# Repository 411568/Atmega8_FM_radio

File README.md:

<h2>🧐 Features</h2>

This project is a revision of one of my old designs, created a long long time ago when atmel atmega chips where still dirty cheap.

It contains two seperate boards: 
 - main_radio_board - this one contains an Atmega8 microcontroller, TEA5767 FM radio module, PAM8302 amplifier module and power connector. 
 - display_and_controls_board - this one is specificly designed to fit in an old Unitra radio case, it has LEDs used as radio frequency indicators, rotary encoder for changing the frequency, potentiometer for volume and some additional buttons.

<h2>📱 Electronics design</h2>

My FM radio is based on the TEA7567 module, that is connected to an Atmega8A-PU microconotroller via I2C. Then it's output goes to the connector, then on the main panel passes through a logarithmic potentiometer for volume control 
and comes back to the PAM8302 D-class amplifier module. I chose it because it works well with my speaker, which is the one used in the original Unitra radio (it is probably over 40 years old and still works very well).

The schematic and PCB were both designed using KiCAD 6.0

<h2>💈 Connector pinouts</h2>

In the image above you can see the 9V DC input jack location, the speaker output connector and two pin headers (IDC connectors).

J4 connector pinout (all of these are generic GPIO pins of the Atmega8):
* 1  - switch 3
* 2  - switch 1
* 3  - NC
* 4  - LE(ED1)
* 5  - SDI
* 6  - switch 4
* 7  - switch 2
* 8  - switch 0
* 9  - OE(ED2)
* 10 - CLK

J3 connector pinout:
* 1  - TEA5767 output (to potentiometer)
* 2  - transistor 0
* 3  - transistor 2
* 4  - encoder B
* 5  - 5V DC
* 6  - 9V DC
* 7  - PAM8302 input (from potentiometer)
* 8  - GND
* 9  - transistor 1
* 10 - encoder A

<h2>📧 Atmega code</h2>

The code is split into several files, you can find them all on my github. 
* encoder.c - containing functions for interfacing with the rotary encoder
* i2c_lib.c - bit banging i2c library
* led_screen.c - functions for interfacing with led driver
* tea5767.c - functions for the TEA5767 FM radio module
* main.c - main program

Main function for the tea5767 is the send_freq function that tells the module to set a certain frequency:

```c
void send_freq()
{
	unsigned char frequencyH;
	unsigned char frequencyL;
	unsigned int frequencyB;

	frequencyB = 4 * (frequency * 1000000 + 225000) / 32768;
	frequencyH = frequencyB >> 8;
	frequencyL = frequencyB & 0xFF;

    //data transmition 
    I2C_Start();
	I2C_Write(TEA5767_ADDRESS_W);
	I2C_Write(frequencyH);
	I2C_Write(frequencyL);
	I2C_Write(0xB0);
	I2C_Write(0x10);
	I2C_Write(0x00);
    I2C_Stop();

    _delay_ms(10);
}
```

and the search function:

```c
void search(uint8_t direction)
{
	unsigned char frequencyH;
	unsigned char frequencyL;
	unsigned int frequencyB;
    double temp = 88.0;

    if(direction == 1)
    {
        temp = frequency + 0.1; 
    }
    else
    {
        temp = frequency - 0.1; 
    }

	frequencyB = 4 * (temp * 1000000 + 225000) / 32768;
	frequencyH = frequencyB >> 8;
	frequencyL = frequencyB & 0xFF;

    I2C_Start();
	I2C_Write(TEA5767_ADDRESS_W); //send address for writing
	I2C_Write(frequencyH |= 0b01000000); //search mode
	I2C_Write(frequencyL);
    if(direction == 1)
    {
        I2C_Write(0b11010000); //search up with mid adc 
    }
    else
    {
        I2C_Write(0b01010000); //search down with mid adc
    }
	I2C_Write(0x10);
	I2C_Write(0x00);

    I2C_Stop();

    _delay_ms(10);
}
```

You can find what the specific bytes being sent to the module mean in its datasheet.

In the main program loop we check the encoder status:

```c
if(val != val_tmp)
{
    if( (val == 3 && val_tmp == 1) || (val == 0 && val_tmp == 2) )
    {
        if(frequency < 108.0)
        {
            frequency += 1.0;
            send_freq(); 
            display(frequency); //display the current frequency
            search(1); //search up from the set freq
        }
    }
    else if( (val == 2 && val_tmp == 0) || (val == 1 && val_tmp == 3) )
    {
        if(frequency > 88.0)
        {
            frequency -= 1.0;
            send_freq();
            display(frequency); //display the current frequency
            search(0); //search down from the set freq
        }
    }
}
```
and change the frequency by 1Hz, then search up from that frequency to fine tune the radio automatically.

In addition to that there are also button inputs:

```c
if(bit_is_clear(button_1_port, button_1_pin)) 
{
    _delay_ms(15); //debounce
    if(bit_is_clear(button_1_port, button_1_pin))
    {
        search(1);
        _delay_ms(500);
        read_freq();
        display(frequency); //display the current frequency
    }
}
```

after pressing the button, the module starts an up search from the current frequency. 
Same aplies to the search down.
You can also change the frequency to one from the predefined tabel by pressing button number 4 or 5.

<h2>💻 Parts list</h2>

As it was just a revision of an older schematic, I did not bother to try and redesign it with newer uC etc. I just used the parts from the previous version (soldered onto a prototype board) or those I had lying around. 
Because of that the design may look a bit peculiar and I decided not to make a BOM file for it. Let me just list them in here for you:
* Atmega8A-PU microcontroller
* TEA5767 module
* PAM8302 amplifier module
* 2x IDC connector for the front panel
* LM317 for power step-down
* 9V DC jack input
* 3x ceramic 100nF capacitor
* 10uF and 4.7uF electrolytic capacitors
* 3x 10k resistor

<h2>📺 Front panel board</h2>

This board is used as my front panel for controls and displaying the current frequency etc.

<h2>💻 Parts list</h2>

* LTV847 optocoupler
* TLC5916IN LED driver
* 3x 1kOhm resistor
* 1.5kOhm resistor
* 5x tact switch
* logarithmic potentiometer for audio control
* rotary encoder
* 2x IDC connector
* a lot of LEDs (red)

<h2>🛡️ License:</h2>

This project is licensed under the MIT License.

<h2> 🙋‍♂️Authors </h2>

- Krzysztof Sikora

<h2>💖Like my work?</h2>

If you have any questions about the project feel free to contact us via email: krzysieksikora717@gmail.com

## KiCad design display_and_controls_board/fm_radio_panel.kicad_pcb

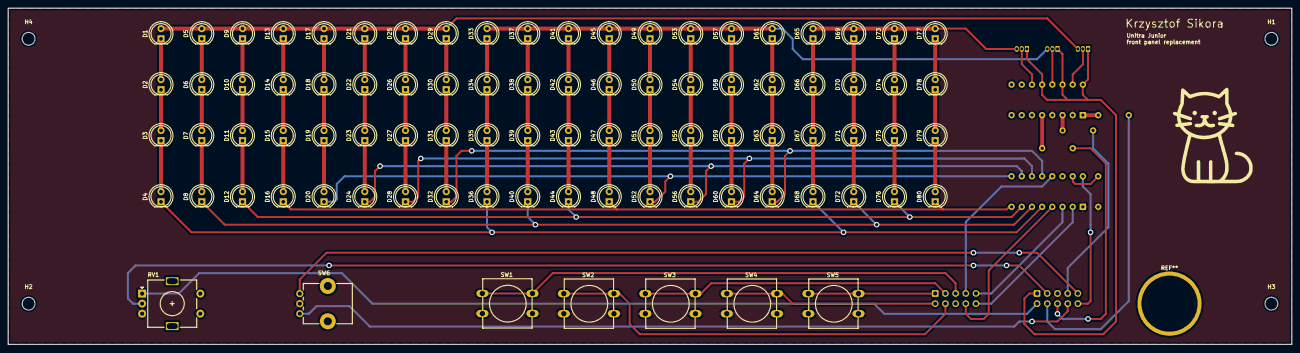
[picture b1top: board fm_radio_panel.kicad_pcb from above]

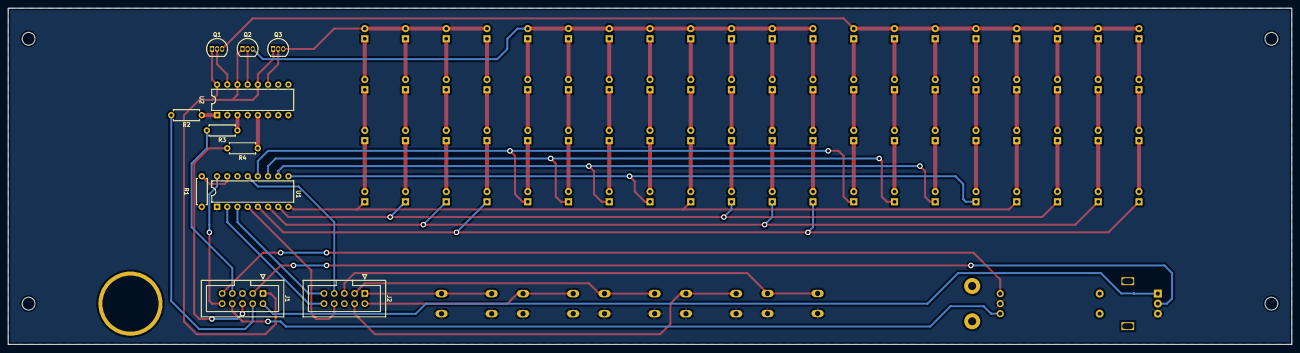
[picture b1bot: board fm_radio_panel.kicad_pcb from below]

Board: 2 copper layers, 320.0 x 83.8 mm, 102 parts (11 on the bottom side), 97 nets.

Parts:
D1, D2, D3, D4, D5, D6, D7, D8, D9, D10, D11, D12, D13, D14, D15, D16, D17, D18, D19, D20, D21, D22, D23, D24, D25, D26, D27, D28, D29, D30, D31, D32, D33, D34, D35, D36, D37, D38, D39, D40, D41, D42, D43, D44, D45, D46, D47, D48, D49, D50, D51, D52, D53, D54, D55, D56, D57, D58, D59, D60, D61, D62, D63, D64, D65, D66, D67, D68, D69, D70, D71, D72, D73, D74, D75, D76, D77, D78, D79, D80: LED; LED_D5.0mm
H1, H2, H3, H4: MountingHole; MountingHole_3.2mm_M3
J1, J2: Conn_02x05_Counter_Clockwise; IDC-Header_2x05_P2.54mm_Vertical
Q1, Q2, Q3: BC547; TO-92_Inline
R1: 1.5k; R_Axial_DIN0207_L6.3mm_D2.5mm_P7.62mm_Horizontal
R2, R3, R4: 1k; R_Axial_DIN0207_L6.3mm_D2.5mm_P7.62mm_Horizontal
RV1: R_Potentiometer; RotaryEncoder_Alps_EC11E-Switch_Vertical_H20mm
SW1, SW2, SW3, SW4, SW5: SW_MEC_5G; SW_PUSH-12mm
SW6: RotaryEncoder; Potentiometer_Alps_RK09K_Single_Vertical
U1: TLC5916IN; DIP-16_W7.62mm
U2: LTV-847; DIP-16_W7.62mm

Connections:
+5V: J1.10, U1.16 (VDD)
+9V: J1.1, Q1.1 (C), Q2.1 (C), Q3.1 (C), U2.12, U2.14, U2.16
AUDIO_AMP: J1.3, RV1.2
AUDIO_L: J1.2, RV1.1
CLK: J2.9, U1.3 (CLK)
GND: J1.5, R1.2, RV1.3, SW1.2, SW2.2, SW3.2, SW4.2, SW5.2, SW6.C, U1.1 (GND), U2.2, U2.4, U2.6
LE(ED1): J2.8, U1.4 (LE(ED1))
unnamed: D1.1 (K), D2.2 (A)
unnamed: D1.2 (A), D5.2 (A), D9.2 (A), D13.2 (A), D17.2 (A), D21.2 (A), D25.2 (A), D29.2 (A), Q1.3 (E)
unnamed: D2.1 (K), D3.2 (A)
unnamed: D3.1 (K), D4.2 (A)
unnamed: D5.1 (K), D6.2 (A)
unnamed: D6.1 (K), D7.2 (A)
unnamed: D7.1 (K), D8.2 (A)
unnamed: D10.1 (K), D11.2 (A)
unnamed: D9.1 (K), D10.2 (A)
unnamed: D11.1 (K), D12.2 (A)
unnamed: D12.1 (K), D44.1 (K), D76.1 (K), U1.7 (OUT2)
unnamed: D13.1 (K), D14.2 (A)
unnamed: D14.1 (K), D15.2 (A)
unnamed: D15.1 (K), D16.2 (A)
unnamed: D16.1 (K), D48.1 (K), D80.1 (K), U1.8 (OUT3)
unnamed: D17.1 (K), D18.2 (A)
unnamed: D18.1 (K), D19.2 (A)
unnamed: D19.1 (K), D20.2 (A)
unnamed: D20.1 (K), D52.1 (K), U1.9 (OUT4)
unnamed: D21.1 (K), D22.2 (A)
unnamed: D22.1 (K), D23.2 (A)
unnamed: D23.1 (K), D24.2 (A)
unnamed: D24.1 (K), D56.1 (K), U1.10 (OUT5)
unnamed: D25.1 (K), D26.2 (A)
unnamed: D26.1 (K), D27.2 (A)
unnamed: D27.1 (K), D28.2 (A)
unnamed: D28.1 (K), D60.1 (K), U1.11 (OUT6)
unnamed: D29.1 (K), D30.2 (A)
unnamed: D30.1 (K), D31.2 (A)
unnamed: D31.1 (K), D32.2 (A)
unnamed: D32.1 (K), D64.1 (K), U1.12 (OUT7)
unnamed: D33.1 (K), D34.2 (A)
unnamed: D33.2 (A), D37.2 (A), D41.2 (A), D45.2 (A), D49.2 (A), D53.2 (A), D57.2 (A), D61.2 (A), Q2.3 (E)
unnamed: D34.1 (K), D35.2 (A)
unnamed: D35.1 (K), D36.2 (A)
unnamed: D4.1 (K), D36.1 (K), D68.1 (K), U1.5 (OUT0)
unnamed: D37.1 (K), D38.2 (A)
unnamed: D38.1 (K), D39.2 (A)
unnamed: D39.1 (K), D40.2 (A)
unnamed: D8.1 (K), D40.1 (K), D72.1 (K), U1.6 (OUT1)
unnamed: D41.1 (K), D42.2 (A)
unnamed: D42.1 (K), D43.2 (A)
unnamed: D43.1 (K), D44.2 (A)
unnamed: D45.1 (K), D46.2 (A)
unnamed: D46.1 (K), D47.2 (A)
unnamed: D47.1 (K), D48.2 (A)
unnamed: D49.1 (K), D50.2 (A)
unnamed: D50.1 (K), D51.2 (A)
unnamed: D51.1 (K), D52.2 (A)
unnamed: D53.1 (K), D54.2 (A)
unnamed: D54.1 (K), D55.2 (A)
unnamed: D55.1 (K), D56.2 (A)
unnamed: D57.1 (K), D58.2 (A)
unnamed: D58.1 (K), D59.2 (A)
unnamed: D59.1 (K), D60.2 (A)
unnamed: D61.1 (K), D62.2 (A)
unnamed: D62.1 (K), D63.2 (A)
unnamed: D63.1 (K), D64.2 (A)
unnamed: D65.1 (K), D66.2 (A)
unnamed: D65.2 (A), D69.2 (A), D73.2 (A), D77.2 (A), Q3.3 (E)
unnamed: D66.1 (K), D67.2 (A)
unnamed: D67.1 (K), D68.2 (A)
unnamed: D69.1 (K), D70.2 (A)
unnamed: D70.1 (K), D71.2 (A)
unnamed: D71.1 (K), D72.2 (A)
unnamed: D73.1 (K), D74.2 (A)
unnamed: D74.1 (K), D75.2 (A)
unnamed: D75.1 (K), D76.2 (A)
unnamed: D77.1 (K), D78.2 (A)
unnamed: D78.1 (K), D79.2 (A)
unnamed: D79.1 (K), D80.2 (A)
unnamed: Q1.2 (B), U2.15
unnamed: Q2.2 (B), U2.13
unnamed: Q3.2 (B), U2.11
unnamed: R1.1, U1.15 (R-EXT)
unnamed: R2.1, U2.1
unnamed: R3.1, U2.3
unnamed: R4.1, U2.5
OE(ED2): J2.7, U1.13 (OE(ED2))
SDI: J2.10, U1.2 (SDI)
encoderA: J1.9, SW6.A
encoderB: J1.8, SW6.B
switch0: J2.5, SW1.1
switch1: J2.4, SW2.1
switch2: J2.3, SW3.1
switch3: J2.2, SW4.1
switch4: J2.1, SW5.1
transistor0: J1.4, R2.2
transistor1: J1.7, R3.2
transistor2: J1.6, R4.2

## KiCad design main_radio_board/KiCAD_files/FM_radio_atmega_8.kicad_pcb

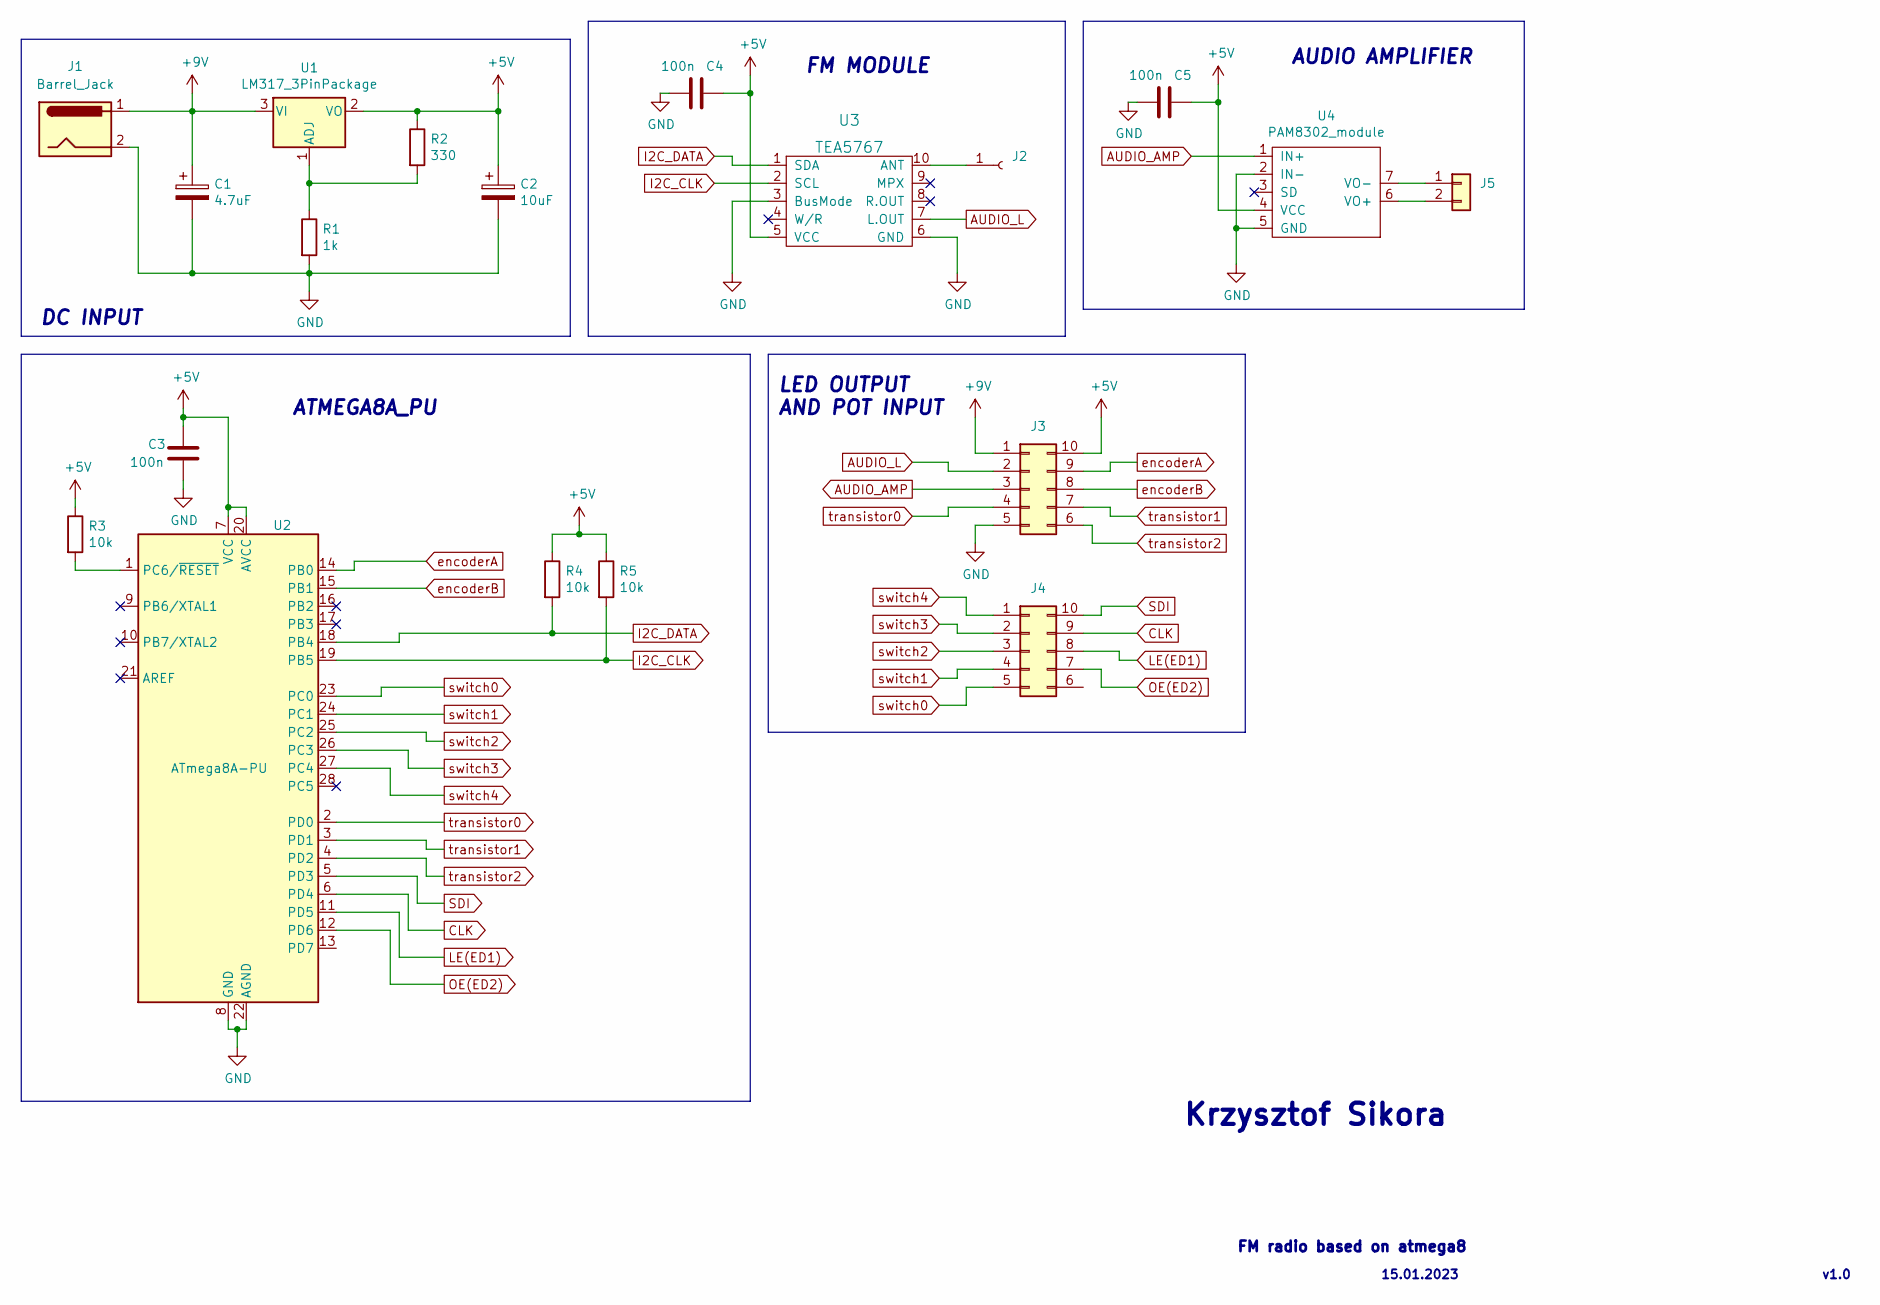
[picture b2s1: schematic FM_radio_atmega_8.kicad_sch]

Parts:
C1: 4.7uF; CP_Radial_D5.0mm_P2.00mm
C2: 10uF; CP_Radial_D5.0mm_P2.00mm
C3, C4, C5: 100n; C_Disc_D5.0mm_W2.5mm_P2.50mm
J1: Barrel_Jack; BarrelJack_Horizontal
J2: Conn_01x01_Female; PinHeader_1x01_P2.54mm_Vertical
J3, J4: Conn_02x05_Counter_Clockwise; PinHeader_2x05_P2.54mm_Vertical
J5: Conn_01x02; SolderWire-1sqmm_1x02_P5.4mm_D1.4mm_OD2.7mm
R1: 1k; R_Axial_DIN0204_L3.6mm_D1.6mm_P7.62mm_Horizontal
R2: 330; R_Axial_DIN0204_L3.6mm_D1.6mm_P7.62mm_Horizontal
R3, R4, R5: 10k; R_Axial_DIN0204_L3.6mm_D1.6mm_P7.62mm_Horizontal
U1: LM317_3PinPackage; TO-220-3_Vertical
U2: ATmega8A-PU; DIP-28_W7.62mm
U3: TEA5767; TEA5767_SMD
U4: PAM8302_module; PAM8302

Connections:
+5V: C2.1, C3.1, C4.1, C5.1, J3.10, R2.1, R3.1, R4.1, R5.1, U1.2 (VO), U2.7 (VCC), U2.20 (AVCC), U3.5 (VCC), U4.4 (VCC)
+9V: C1.1, J1.1, J3.1, U1.3 (VI)
AUDIO_AMP: J3.3, U4.1 (IN+)
AUDIO_L: J3.2, U3.7 (L.OUT)
CLK: J4.9, U2.6 (PD4)
GND: C1.2, C2.2, C3.2, C4.2, C5.2, J1.2, J3.5, R1.2, U2.8 (GND), U2.22 (AGND), U3.3 (BusMode), U3.6 (GND), U4.2 (IN-), U4.5 (GND)
I2C_CLK: R5.2, U2.19 (PB5), U3.2 (SCL)
I2C_DATA: R4.2, U2.18 (PB4), U3.1 (SDA)
LE(ED1): J4.8, U2.11 (PD5)
unnamed: J2.1, U3.10 (ANT)
unnamed: J5.1, U4.7 (VO-)
unnamed: J5.2, U4.6 (VO+)
unnamed: R1.1, R2.2, U1.1 (ADJ)
unnamed: R3.2, U2.1 (PC6/~RESET)
OE(ED2): J4.7, U2.12 (PD6)
SDI: J4.10, U2.5 (PD3)
encoderA: J3.9, U2.14 (PB0)
encoderB: J3.8, U2.15 (PB1)
switch0: J4.5, U2.23 (PC0)
switch1: J4.4, U2.24 (PC1)
switch2: J4.3, U2.25 (PC2)
switch3: J4.2, U2.26 (PC3)
switch4: J4.1, U2.27 (PC4)
transistor0: J3.4, U2.2 (PD0)
transistor1: J3.7, U2.3 (PD1)
transistor2: J3.6, U2.4 (PD2)

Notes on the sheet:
DC INPUT
v1.0
LED OUTPUT AND POT INPUT
Krzysztof Sikora
15.01.2023
AUDIO AMPLIFIER
ATMEGA8A_PU
FM MODULE
FM radio based on atmega8

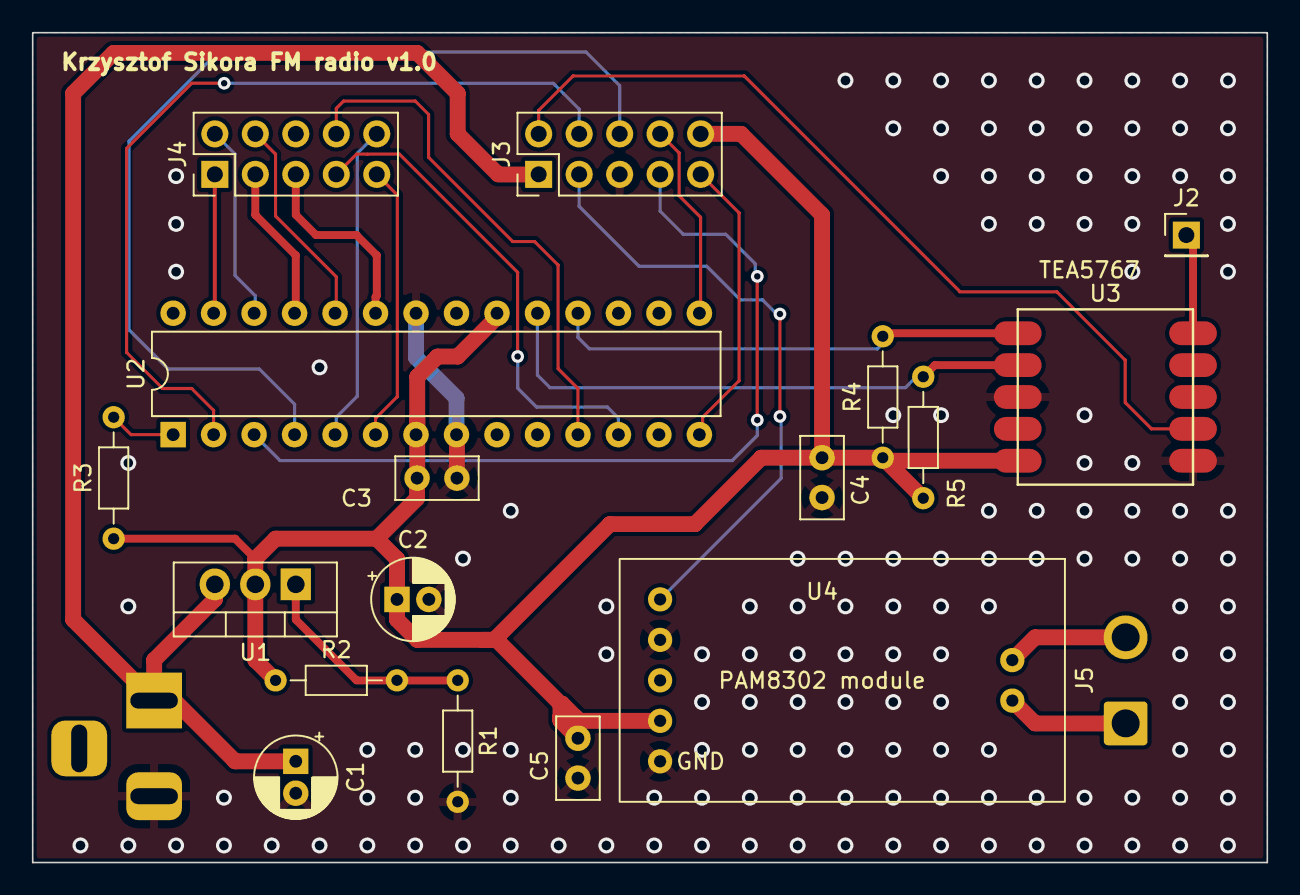
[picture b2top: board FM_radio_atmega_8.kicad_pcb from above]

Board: 2 copper layers, 77.5 x 52.1 mm, 19 parts (1 on the bottom side), 26 nets.

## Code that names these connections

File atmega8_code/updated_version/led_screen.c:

#include <avr/io.h>
#include <util/delay.h>
#include <stdio.h>
#include <string.h>
#include <math.h>
#include "tea5767.c"

#define _BV(bit)			(1 << (bit))
#define bit_is_set(sfr, bit)		(_SFR_BYTE(sfr) & _BV(bit))
#define bit_is_clear(sfr, bit)		(!(_SFR_BYTE(sfr) & _BV(bit)))

#define encoder_port PINB
#define A_pin PB0
#define B_pin PB1

#define OE PD6
#define LE PD5


void animate()
{
    for(double i = 88.0; i < 108.0; i = i + 1.0)
    {
        display(i);
        _delay_ms(1);
    }
    for(double i = 107.0; i > 88.0; i = i - 1.0)
    {
        display(i);
        _delay_ms(1);
    }
}


//displays the current frequency
void display(double input)
{
    uint8_t led_strip;
    
    uint8_t curr_freq = floor(input) - 88;
    
    //should never occur
    if(curr_freq < 0) 
        curr_freq = 0;
    if(curr_freq > 19)
        curr_freq = 19;

    //setting the optocouplers
    if(curr_freq < 8)
    {
        PORTD |= (1 << PD0);
        PORTD &= ~(1 << PD1);
        PORTD &= ~(1 << PD2);
    }
    else if(curr_freq < 16)
    {
        PORTD &= ~(1 << PD0);
        PORTD |= (1 << PD1);
        PORTD &= ~(1 << PD2);
    }
    else
    {
        PORTD &= ~(1 << PD0);
        PORTD &= ~(1 << PD1);
        PORTD |= (1 << PD2);
    }

    //setting the led driver
    uint8_t temp8 = curr_freq % 8; //data for the driver
    temp8 = 8 - temp8;
    uint8_t curr_freq_8 = 0;                                   
    if(temp8 > 0)
        curr_freq_8 = 1 << (temp8 - 1);

    PORTD &= ~(1 << LE); //LE to low
    PORTD |= (1 << OE); // OE to high - output off
    _delay_ms(1);

	for(int i = 0; i < 8; i++)
	{
		if(curr_freq_8 & (1 << i)) 
		{
            PORTD |= (1 << PD3); //set SDI high
            _delay_ms(1);
            PORTD |= (1 << PD4); //set clock high
            _delay_ms(1);
        }
        else
        {
            PORTD &= ~(1 << PD3); //set SDI low
            _delay_ms(1);
            PORTD |= (1 << PD4); //set clock high
            _delay_ms(1);
        }
        PORTD &= ~(1 << PD4); //set clock low
    }

    _delay_ms(1);
    PORTD |= (1 << LE); //set LE high for some time
    _delay_ms(1);
    PORTD &= ~(1 << LE); //LE to low
    _delay_ms(1);
    PORTD &= ~(1 << OE); //OE to low - turn the output ON
}

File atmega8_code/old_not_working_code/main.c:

#include <avr/io.h>
#include <util/delay.h>
#include <avr/power.h>

#include "pinDefines.h"
#include "i2c.h"

#define _BV(bit)			(1 << (bit))
#define bit_is_set(sfr, bit)		(_SFR_BYTE(sfr) & _BV(bit))
#define bit_is_clear(sfr, bit)		(!(_SFR_BYTE(sfr) & _BV(bit)))

#define TEA5767_ADDRESS_W               0b11000000	 //address for writing to the TEA5767 (0xC0)


//NOTE: those are old pin defines, have to change them later
#define TLC5916_CLK	            	PB3 			 //clk port for the led driver
#define TLC5916_SDI			PB2			             //data port 
#define TLC5916_LEED1			PB1 			     //port LE(ED1) 
#define TLC5916_OEED2			PB4			         //port OE(ED2) 

#define PC847_1				PC1			             //port pierwszego transoptora
#define PC847_2				PC2		             	 //port drugiego transoptora
#define PC847_3				PC3			             //port trzeciego transoptora

#define button_1			PD0			             //port przycisku frequency++
#define button_2			PD1			             //port przycisku frequency--

#define debounce_t 		 	20



//global variables
double frequency;
double frequencytab[] = {89.2, 91.5, 95.7, 96.4, 97.6, 99.7, 102.2, 104.5, 105, 106.7};
int station_number;



// send the frequency to the TEA module
void send_freq()
{
	unsigned char frequencyH;
	unsigned char frequencyL;
	unsigned int frequencyB;

	frequencyB = 4 * (frequency * 1000000 + 225000) / 32768;
	frequencyH = frequencyB >> 8;
	frequencyL = frequencyB & 0xFF;

    //data transmition 
	i2cStart();
	i2cSend(TEA5767_ADDRESS_W);
	i2cSend(frequencyH);
	i2cSend(frequencyL);
	i2cSend(0xB0);
	i2cSend(0x10);
	i2cSend(0x00);
	i2cStop();
}


void LED_loop(char setting)
{
	for(int i = 0; i < 8; i++)
	{
		if(setting & (1 << i)) //if the bit in "setting" is set to "1" then it sends a "1" to the serial port
		{
			PORTB = 0b00010100;
			_delay_ms(2);
			PORTB = 0b00011100;
			_delay_ms(2);

		}
		else
		{
			PORTB = 0b00010000;
			_delay_ms(2);
			PORTB = 0b00011000;
			_delay_ms(2);

		}
	}
}



//led set
void LED_send(char setting, int opto)
{
	PORTC = 2 << opto; //testing this option now

	if(opto == 0) //jeszcze nie wiem co ma tu byc
	{
		LED_loop(setting);
	}
	else if(opto == 1) //jesli jestem na srodku tam gdzie sa zamienione diody
	{
		char temporary = setting;
		setting = setting >> 2;

		if(temporary && 0x02 == 0x02)
		{
			setting = setting || 0x80;
		}
		if(temporary && 0x01 == 0x01)
		{
			setting = setting || 0x40;
		}

		LED_loop(setting);
	}
	else if(opto == 2) //tu jest chyba wszystko ok
	{
		LED_loop(setting);
	}


	_delay_ms(2);
	PORTB = 0b00010010;
	_delay_ms(2);
	PORTB = 0b00000000;
	_delay_ms(2);
}


//led animation
void animateLED()
{
	for(int i = 0; i < 8; i++)
	{
		LED_send(1 << i, 1); //te bity sa na odwrot na wyswietlaczu
		_delay_ms(10);
	}
	LED_send(0b10101010, 0); //od lewej bity sa od lewej na wyswietlaczu (chyba)
	_delay_ms(100);
	LED_send(0b01000001, 2); //tu sa 3 srodkowe bity ktores XDDD
	_delay_ms(100);
	LED_send(0b11000010, 1); //tutaj 7 i 8 sa na miejscu 1 i 2 a reszta jest przesunieta
}

void setup()
{
	initI2C();
	DDRB = 0xFF; //port B w trybie wyjścia
	DDRC = 0xFF; //port C w trybie wyjścia
	DDRD = 0x00; //port D ustawiony w tryb wejścia
	PORTD = 0x3; //ustawienie oporników podciągających (tylko piny PD0 i PD1)


    //for testing only
	animateLED();

    //starting frequency from the table
	frequency = frequencytab[0];
	station_number = 0;
	send_freq();
	_delay_ms(100);
}



// -------- MAIN -------- //
int main(void)
{
	setup();

	while(1)
	{
		// ------ Zwiększenie częstotliwości ------ //
		if(bit_is_clear(PIND, button_1))
		{
			_delay_ms(debounce_t);
			if(bit_is_clear(PIND, button_1))
			{
				if(station_number < 9)
					station_number++;
				else
					station_number = 0;

				frequency = frequencytab[station_number];
				send_freq();
			}
		}


		// ------ Zmniejszanie częstotliwości ------ //
		if(bit_is_clear(PIND, button_2))
		{
			_delay_ms(debounce_t);
			if(bit_is_clear(PIND, button_2))
			{
				if(station_number > 0)
					station_number--;
				else
					station_number = 9;

				frequency = frequencytab[station_number];
				send_freq();
			}
		}
	}

	return (0);
}

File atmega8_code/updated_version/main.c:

//TODO
//Fix searching for stations
//find a better way to set frequency via rotary encoder

#ifndef F_CPU
#define F_CPU	8000000
#endif

#include <avr/io.h>
#include <util/delay.h>
#include <stdio.h>
#include <string.h>

//#include "tea5767.c"
#include "encoder.c"
#include "led_screen.c"


#define _BV(bit)			(1 << (bit))
#define bit_is_set(sfr, bit)		(_SFR_BYTE(sfr) & _BV(bit))
#define bit_is_clear(sfr, bit)		(!(_SFR_BYTE(sfr) & _BV(bit)))

#define button_1_pin PC0
#define button_1_port PINC

#define button_2_pin PC1
#define button_2_port PINC

#define button_3_pin PC2
#define button_3_port PINC

#define button_4_pin PC3
#define button_4_port PINC

#define button_5_pin PC4
#define button_5_port PINC


int main(void)
{
    //setup the I2C, start TEA5767 with frequency from the table
	setup();
                  
	//setup GPIO
    DDRC = 0x00; //C pins as inputs 
    DDRB = 0x00; //B pins as inputs 
    DDRD = 0xFF; //D pins as outputs
    PORTC = 0xFF; //C pins with internal pullup resistors
    PORTB = 0xFF; //C pins with internal pullup resistors
    

    //for rotary encoder
    uint8_t val_tmp = 0;
    uint8_t val = 0;
    val_tmp = read_encoder();

    //for station tab
    uint8_t station_number = 0;

    //enable led display
    display(frequency);

	//main loop
	while(1)
	{
		// ------ ENCODER ------ //
        val_tmp = read_encoder();

        if(val != val_tmp)
        {
            if( (val == 3 && val_tmp == 1) || (val == 0 && val_tmp == 2) )
            {
                if(frequency < 108.0)
                {
                    frequency += 1.0;
                    send_freq(); 
                    display(frequency); //display the current frequency
                    search(1); //search up from the set freq
                }
            }
            else if( (val == 2 && val_tmp == 0) || (val == 1 && val_tmp == 3) )
            {
                if(frequency > 88.0)
                {
                    frequency -= 1.0;
                    send_freq();
                    display(frequency); //display the current frequency
                    search(0); //search down from the set freq
                }
            }
        }

        val = val_tmp;


		// ------ SEARCH UP ------ //
		if(bit_is_clear(button_1_port, button_1_pin)) 
		{
			_delay_ms(15); //debounce
			if(bit_is_clear(button_1_port, button_1_pin))
			{
                search(1);
                _delay_ms(500);
                read_freq();
                display(frequency); //display the current frequency
			}
		}


		// ------ SEARCH DOWN ------ //
		if(bit_is_clear(button_2_port, button_2_pin)) 
		{
			_delay_ms(15); //debounce
			if(bit_is_clear(button_2_port, button_2_pin))
			{
                search(0);
                _delay_ms(500);
                read_freq();
                display(frequency); //display the current frequency
			}
		}


		// ------ ANIMATION ------ //
		if(bit_is_clear(button_3_port, button_3_pin)) 
		{
			_delay_ms(15); //debounce
			if(bit_is_clear(button_3_port, button_3_pin))
			{
                animate();
			}
		}


		// ------ TAB UP ------ //
		if(bit_is_clear(button_4_port, button_4_pin)) 
		{
			_delay_ms(15); //debounce
			if(bit_is_clear(button_4_port, button_4_pin))
			{
                if(station_number < 10)
                    station_number++;
                else
                    station_number = 0;
                frequency = frequencytab[station_number];
                display(frequency); //display the current frequency
                send_freq();
			}
		}


		// ------ TAB DOWN ------ //
		if(bit_is_clear(button_5_port, button_5_pin)) 
		{
			_delay_ms(15); //debounce
			if(bit_is_clear(button_5_port, button_5_pin))
			{
                if(station_number > 0)
                    station_number--;
                else
                    station_number = 10;
                frequency = frequencytab[station_number];
                display(frequency); //display the current frequency
                send_freq();
			}
		}
	}
}

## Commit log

2023-01-18 Added: new folders
2023-01-18 Added: new readme
2023-01-18 Changed: readme
2023-01-18 Added: old atmega code
2023-01-18 Added: TEA5767 lib
2023-01-26 new code
2023-02-08 deleted lib
2023-02-08 renamed folder
2023-02-09 tea5767 lib created
2023-02-09 added searching for stations
2023-02-09 added todo note
2023-02-19 front panel added
2023-02-26 code update
2023-03-06 code changes
2025-01-30 Create LICENSE
